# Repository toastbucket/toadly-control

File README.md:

View this project on [CADLAB.io](https://cadlab.io/project/26355). 

# toadly-control

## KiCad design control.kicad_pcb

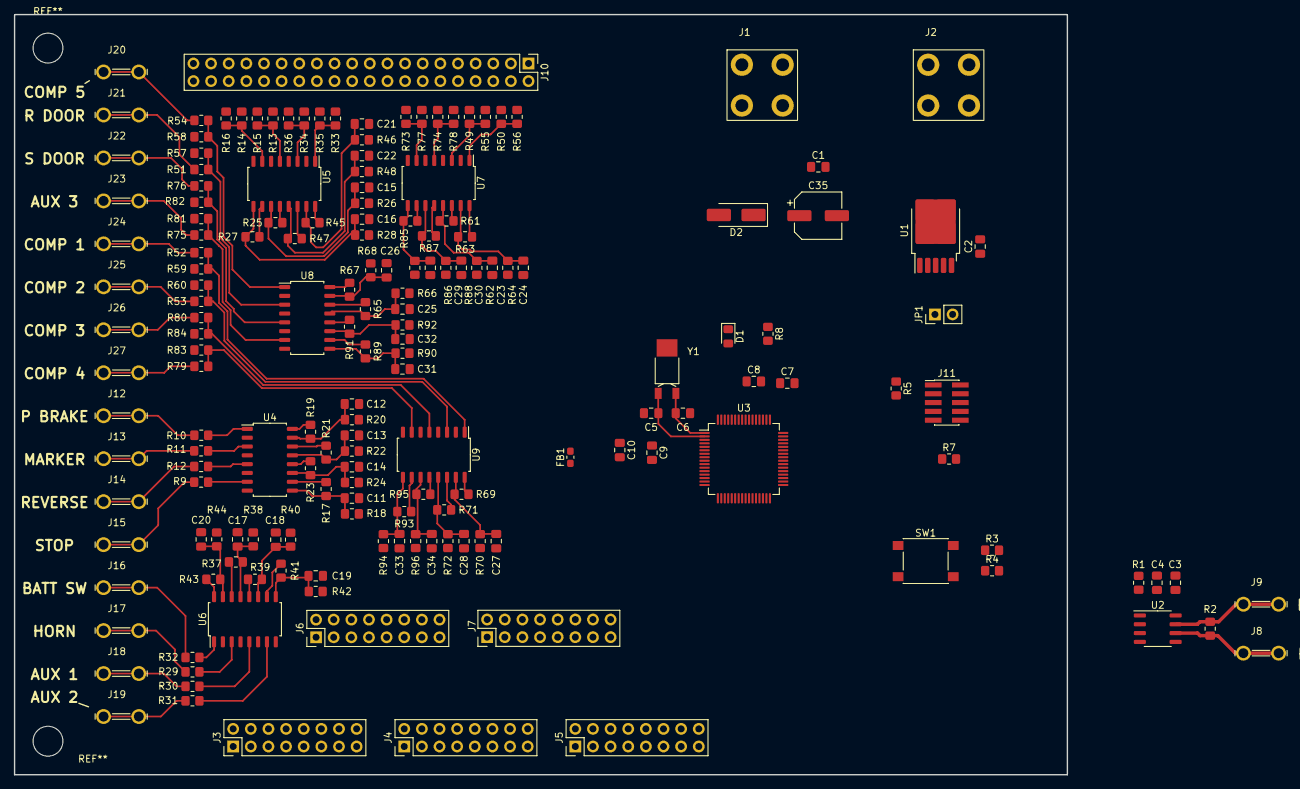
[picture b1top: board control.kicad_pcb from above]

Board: 4 copper layers, 151.6 x 109.5 mm, 172 parts (0 on the bottom side), 111 nets.

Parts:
C1, C4, C11, C12, C13, C14, C15, C16, C17, C18, C19, C20, C21, C22, C23, C24, C25, C26, C27, C28, C29, C30, C31, C32, C33, C34: 1uF; C_0805_2012Metric_Pad1.18x1.45mm_HandSolder
C2: 10uF; C_0805_2012Metric_Pad1.18x1.45mm_HandSolder
C3, C7, C8, C9: 0.1uF; C_0805_2012Metric_Pad1.18x1.45mm_HandSolder
C5, C6: 6.8pF; C_0805_2012Metric_Pad1.18x1.45mm_HandSolder
C10: 10uF/16V; C_0805_2012Metric_Pad1.18x1.45mm_HandSolder
C35: 22uF; CP_Elec_6.3x7.7
D1: LED; LED_0805_2012Metric_Pad1.15x1.40mm_HandSolder
D2: D; D_SMA_Handsoldering
FB1: BLM18PG181SN1D; L_0603_1608Metric_Pad1.05x0.95mm_HandSolder
J1, J2: Wurth_THR_Terminal_M4
J3, J4, J5, J6, J7: Conn_02x08_Odd_Even; PinHeader_2x08_P2.54mm_Vertical
J8, J9, J12, J13, J14, J15, J16, J17, J18, J19, J20, J21, J22, J23, J24, J25, J26, J27: TE_Faston_20-16AWG_Straight_Tab
J10: Conn_02x20_Odd_Even; PinHeader_2x20_P2.54mm_Vertical
J11: Conn_ARM_JTAG_SWD_10; PinHeader_2x05_P1.27mm_Vertical_SMD
JP1: Jumper_2_Open; PinHeader_1x02_P2.54mm_Vertical
R1: 10K; R_0805_2012Metric_Pad1.20x1.40mm_HandSolder
R2: 120; R_0805_2012Metric_Pad1.20x1.40mm_HandSolder
R3: 100K; R_0805_2012Metric_Pad1.20x1.40mm_HandSolder
R4, R7: 39; R_0805_2012Metric_Pad1.20x1.40mm_HandSolder
R5, R13, R14, R17, R19, R21, R23, R25, R27, R33, R34, R37, R39, R41, R43, R45, R47, R49, R50, R51, R52, R53, R54, R61, R63, R65, R67, R69, R71, R73, R74, R76, R79, R80, R81, R85, R87, R89, R91, R93, R95: DNP; R_0805_2012Metric_Pad1.20x1.40mm_HandSolder
R8: 91; R_0805_2012Metric_Pad1.20x1.40mm_HandSolder
R9, R10, R11, R12, R15, R16, R29, R30, R31, R32, R35, R36, R55, R56, R57, R58, R59, R60, R75, R77, R78, R82, R83, R84: 3.3k; R_0805_2012Metric_Pad1.20x1.40mm_HandSolder
R18, R20, R22, R24, R26, R28, R38, R40, R42, R44, R46, R48, R62, R64, R66, R68, R70, R72, R86, R88, R90, R92, R94, R96: 1.1k; R_0805_2012Metric_Pad1.20x1.40mm_HandSolder
SW1: SW_Push; SW_Push_1P1T_NO_6x6mm_H9.5mm
U1: TPS7B8733; TO-252-5_TabPin3
U2: MAX33071; SO-8_3.9x4.9mm_P1.27mm
U3: ATSAMD21J18A-A; TQFP-64_10x10mm_P0.5mm
U4, U5, U6, U7, U8, U9: TCMT4600; SOP-16_4.55x10.3mm_P1.27mm
Y1: 32.768kHz; Crystal_SMD_MicroCrystal_MS1V-T1K

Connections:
+3.3V: C2.1, C3.1, C4.1, C8.1, FB1.2, JP1.2 (B), R3.2, R8.2, R17.2, R19.2, R21.2, R23.2, R25.2, R27.2, R37.2, R39.2, R41.2, R43.2, R45.2, R47.2, R61.2, R63.2, R65.2, R67.2, R69.2, R71.2, R85.2, R87.2, R89.2, R91.2, R93.2, R95.2, U1.5 (OUT), U2.8 (VCC), U3.21 (VDDIO), U3.34 (VDDIO), U3.48 (VDDIO), U3.56 (VDDIN), U4.10, U4.12, U4.14, U4.16, U5.10, U5.12, U5.14, U5.16, U6.10, U6.12, U6.14, U6.16, U7.10, U7.12, U7.14, U7.16, U8.10, U8.12, U8.14, U8.16, U9.10, U9.12, U9.14, U9.16
+12V: C1.1, C35.1, D2.1 (K), J10.1, J10.2, J10.3, J10.4, J10.37, J10.38, J10.39, J10.40, R15.2, R16.2, R35.2, R36.2, R55.2, R56.2, R57.2, R58.2, R59.2, R60.2, R77.2, R78.2, R81.2, R82.2, R83.2, R84.2, U1.1 (IN)
/MCU/#RESET: R3.1, R4.2, R7.2, U3.52 (~RESET)
/MCU/SWDCLK: J11.4 (SWCLK/TCK), U3.57 (PA30)
/MCU/SWDIO: J11.2 (SWDIO/TMS), U3.58 (PA31)
/RS485_A: J8.1, J8.2 (P1), J10.9, R2.1, U2.6 (A)
/RS485_B: J9.1, J9.2 (P1), J10.10, R2.2, U2.7 (B)
AUX_1_EN: J6.6, U3.16 (PA07)
AUX_1_SENSE: C18.1, R39.1, R40.2, U3.35 (PA16), U6.11
AUX_2_EN: J6.8, U3.46 (PA25)
AUX_2_SENSE: C19.1, R41.1, R42.2, U3.36 (PA17), U6.9
AUX_3_EN: J6.10, U3.51 (PA27)
AUX_3_SENSE: C31.1, R89.1, R90.2, U3.37 (PA18), U8.9
AUX_4_EN: J7.6, U3.53 (PA28)
AUX_5_EN: J7.8, U3.60 (PB31)
BACKUP_CHIME_EN: J4.8, U3.4 (PA03)
BATT_SW_SENSE: C20.1, R43.1, R44.2, U3.32 (PA15), U6.15
CAB_1_SENSE: C16.1, R27.1, R28.2, U3.26 (PB13), U5.9
CAB_2_SENSE: C15.1, R25.1, R26.2, U3.27 (PB14), U5.11
CAB_3_SENSE: C22.1, R47.1, R48.2, U3.28 (PB15), U5.13
CAB_4_SENSE: C21.1, R45.1, R46.2, U3.39 (PB16), U5.15
CAB_5_SENSE: C24.1, R63.1, R64.2, U3.40 (PB17), U7.15
CAB_6_SENSE: C23.1, R61.1, R62.2, U3.38 (PA19), U7.13
CAB_7_SENSE: C30.1, R87.1, R88.2, U3.41 (PA20), U7.11
CAB_8_SENSE: C29.1, R85.1, R86.2, U3.42 (PA21), U7.9
CAB_CHIME_EN: J4.6, U3.3 (PA02)
CAB_SIGNAL_1: J10.11, J10.13, R14.2
CAB_SIGNAL_2: J10.15, J10.17, R13.2
CAB_SIGNAL_3: J10.19, J10.21, R34.2
CAB_SIGNAL_4: J10.23, J10.25, R33.2
CAB_SIGNAL_5: J10.12, J10.14, R50.2
CAB_SIGNAL_6: J10.16, J10.18, R49.2
CAB_SIGNAL_7: J10.20, J10.22, R74.2
CAB_SIGNAL_8: J10.24, J10.26, R73.2
COMP_1_LGT_EN: J5.6, U3.64 (PB03)
COMP_1_SENSE: C27.1, R69.1, R70.2, U3.11 (PB08), U9.15
COMP_2_LGT_EN: J5.8, U3.5 (PB04)
COMP_2_SENSE: C28.1, R71.1, R72.2, U3.12 (PB09), U9.13
COMP_3_LGT_EN: J5.10, U3.6 (PB05)
COMP_3_SENSE: C34.1, R95.1, R96.2, U3.23 (PB10), U9.11
COMP_4_LGT_EN: J5.12, U3.9 (PB06)
COMP_4_SENSE: C33.1, R93.1, R94.2, U3.24 (PB11), U9.9
COMP_5_LGT_EN: J5.14, U3.10 (PB07)
COMP_5_SENSE: C26.1, R67.1, R68.2, U3.25 (PB12), U8.15
FLOOD_D_EN: J3.6, J3.8, U3.61 (PB00)
FLOOD_P_EN: J3.14, J3.16, U3.63 (PB02)
FLOOD_R_EN: J3.10, J3.12, U3.62 (PB01)
FOG_LGT_EN: J4.10, J4.12, U3.13 (PA04)
GNDREF: C1.2, C2.2, C3.2, C4.2, C5.1, C6.1, C7.2, C8.2, C9.1, C10.1, C11.2, C12.2, C13.2, C14.2, C15.2, C16.2, C17.2, C18.2, C19.2, C20.2, C21.2, C22.2, C23.2, C24.2, C25.2, C26.2, C27.2, C28.2, C29.2, C30.2, C31.2, C32.2, C33.2, C34.2, C35.2, J2.1, J10.5, J10.6, J10.7, J10.8, J10.33, J10.34, J10.35, J10.36, J11.3 (GND), J11.5 (GND), J11.9 (GNDDetect), R1.2, R5.2, R18.1, R20.1, R22.1, R24.1, R26.1, R28.1, R38.1, R40.1, R42.1, R44.1, R46.1, R48.1, R62.1, R64.1, R66.1, R68.1, R70.1, R72.1, R86.1, R88.1, R90.1, R92.1, R94.1, R96.1, SW1.1, U1.3 (GND), U2.5 (GND), U3.7 (GNDANA), U3.22 (GND), U3.33 (GND), U3.47 (GND), U3.54 (GND), U4.2, U4.4, U4.6, U4.8, U5.2, U5.4, U5.6, U5.8, U6.2, U6.4, U6.6, U6.8, U7.2, U7.4, U7.6, U7.8, U8.2, U8.4, U8.6, U8.8, U9.2, U9.4, U9.6, U9.8, Y1.3
HORN_SENSE: C17.1, R37.1, R38.2, U3.29 (PA12), U6.13
ISECT_D_EN: J4.14, U3.14 (PA05)
ISECT_P_EN: J4.16, U3.15 (PA06)
MARKER_LIGHT_SENSE: C13.1, R21.1, R22.2, U3.18 (PA09), U4.13
unnamed: D1.2 (A), R8.1
unnamed: D1.1 (K), U3.59 (PB30)
unnamed: D2.2 (A), J1.1
unnamed: J11.1 (VTref), JP1.1 (A), R5.1
unnamed: J11.10 (~RESET), R7.1
unnamed: J12.1, J12.2 (P1), R10.1
unnamed: J13.1, J13.2 (P1), R11.1
unnamed: J14.1, J14.2 (P1), R12.1
unnamed: J15.1, J15.2 (P1), R9.1
unnamed: J16.1, J16.2 (P1), R32.1
unnamed: J17.1, J17.2 (P1), R29.1
unnamed: J18.1, J18.2 (P1), R30.1
unnamed: J19.1, J19.2 (P1), R31.1
unnamed: J20.1, J20.2 (P1), R54.2
unnamed: J21.1, J21.2 (P1), R51.2
unnamed: J22.1, J22.2 (P1), R76.2
unnamed: J23.1, J23.2 (P1), R75.2
unnamed: J24.1, J24.2 (P1), R52.2
unnamed: J25.1, J25.2 (P1), R53.2
unnamed: J26.1, J26.2 (P1), R80.2
unnamed: J27.1, J27.2 (P1), R79.2
unnamed: R4.1, SW1.2
unnamed: R9.2, U4.7
unnamed: R10.2, U4.1
unnamed: R11.2, U4.3
unnamed: R12.2, U4.5
unnamed: R13.1, R15.1, U5.5
unnamed: R14.1, R16.1, U5.7
unnamed: R29.2, U6.3
unnamed: R30.2, U6.5
unnamed: R31.2, U6.7
unnamed: R32.2, U6.1
unnamed: R33.1, R35.1, U5.1
unnamed: R34.1, R36.1, U5.3
unnamed: R49.1, R55.1, U7.3
unnamed: R50.1, R56.1, U7.1
unnamed: R51.1, R57.1, U8.3
unnamed: R52.1, R59.1, U9.1
unnamed: R53.1, R60.1, U9.3
unnamed: R54.1, R58.1, U8.1
unnamed: R73.1, R77.1, U7.7
unnamed: R74.1, R78.1, U7.5
unnamed: R75.1, R81.1, U8.7
unnamed: R76.1, R82.1, U8.5
unnamed: R79.1, R83.1, U9.7
unnamed: R80.1, R84.1, U9.5
unnamed: C6.2, U3.1 (PA00), Y1.1
unnamed: C5.2, U3.2 (PA01), Y1.2
unnamed: C9.2, C10.2, FB1.1, U3.8 (VDDANA)
unnamed: C7.1, U3.55 (VDDCORE)
PARK_BRAKE_SENSE: C12.1, R19.1, R20.2, U3.17 (PA08), U4.15
REAR_DOOR_SENSE: C25.1, R65.1, R66.2, U3.31 (PA14), U8.13
REVERSE_LIGHT_SENSE: C14.1, R23.1, R24.2, U3.20 (PA11), U4.11
RS485_DATA_ENABLE: R1.1, U2.2 (RE#), U2.3 (DE), U3.45 (PA24)
SIDE_DOOR_SENSE: C32.1, R91.1, R92.2, U3.30 (PA13), U8.11
STOP_LIGHT_SENSE: C11.1, R17.1, R18.2, U3.19 (PA10), U4.9
UART3_RX: U2.1 (RO), U3.44 (PA23)
UART3_TX: U2.4 (DI), U3.43 (PA22)

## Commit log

2022-12-27 add Arduino Nano BLE base circuit
2022-12-27 add toadly symbol submodule
2022-12-27 update symbols to include max337x and pca
2022-12-27 create IO busses
2022-12-28 add analog pins to IO and I2C pullup slots
2022-12-28 update symbols
2022-12-28 add MAX33071
2022-12-28 add 40pin IDC connector
2022-12-28 add IO page and flood light drivers
2022-12-28 rename IO to Drivers
2022-12-28 add truck drivers
2022-12-28 add Faston connectors for RS485
2022-12-28 add horn circuit
2022-12-28 add signal inputs
2022-12-28 Backlink to CADLAB.io has been added.
2022-12-30 add horn sense
2022-12-30 select 1n4148w for horn flywheel diode
2022-12-30 add horn jumper to allow mcu or hardware control
2023-01-04 add power input
2023-01-04 annotate schematic
2023-01-04 fix RS485 control IO
2023-01-04 add pulldowns for flood light driver control lines
2023-01-04 add header footprints
2023-01-16 add basic TVS
2023-01-17 update footprints
2024-03-11 many changes, update to KiCAD 7
2024-03-15 add compartment lights, switch to samd21j
2024-03-21 remove drivers
2024-04-03 add cab signals and connect inputs
2024-04-12 connect signals to connectors, start layout
2024-04-25 begin grouping parts
2024-04-28 route sense input tracks
2024-04-29 lay pre-autorouting tracks
2024-04-30 route all tracks
2024-04-30 fix DRC errors
2024-04-30 add revision information
2024-04-30 generate pedigree A
2024-05-01 update layout and add some series resistors
2024-05-01 add IO expander and additional AUX outputs
2024-05-01 generate pedigree B
2024-10-14 update to kicad 8
